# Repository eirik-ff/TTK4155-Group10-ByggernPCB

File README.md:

# TTK4155-Group10-ByggernPCB
The PCB files for the NTNU course Byggern (TTK4155 - Embedded and Industrial Computer Systems Design). 

# Schematic

# PCB Render

## Notes

USB module doesn't work.

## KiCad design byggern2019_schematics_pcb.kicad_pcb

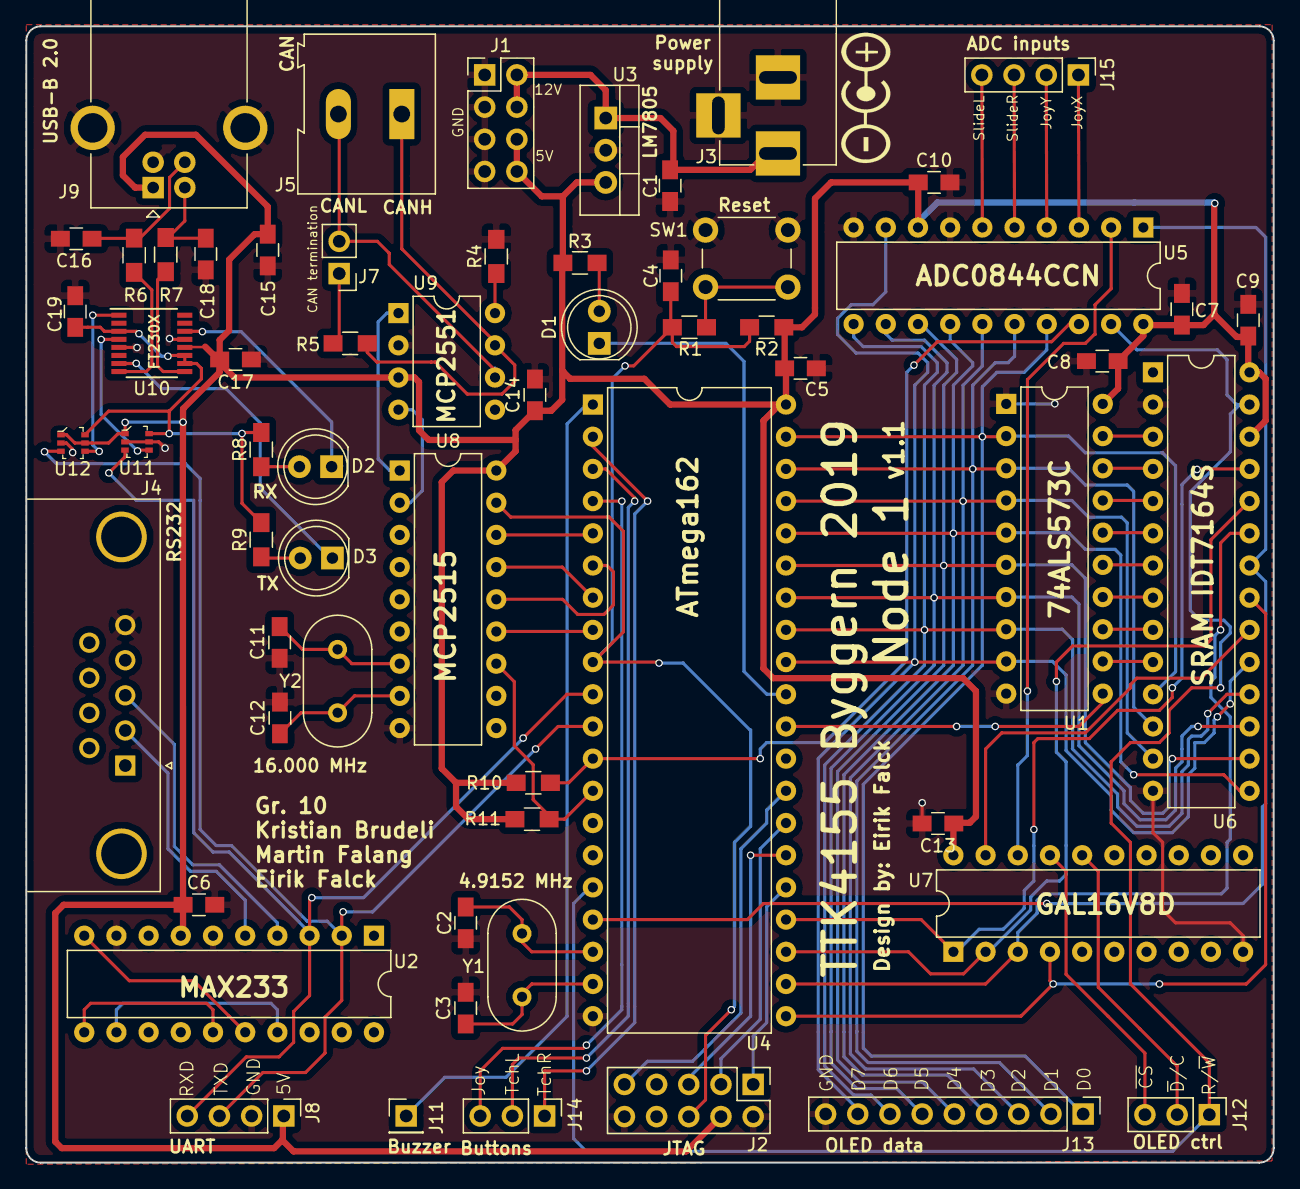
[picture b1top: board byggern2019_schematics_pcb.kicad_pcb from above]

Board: 2 copper layers, 98.4 x 89.7 mm, 61 parts (0 on the bottom side), 80 nets.

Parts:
C1, C4, C5, C6, C7, C8, C9, C10, C13, C14, C15, C19: 1u; C_0805_HandSoldering
C2, C3, C11, C12: 22p; C_0805_HandSoldering
C16, C18: 47p; C_0805_HandSoldering
C17: 10n; C_0805_HandSoldering
D1: Heartbeat; LED_D5.0mm
D2: ~RXLED; LED_D5.0mm
D3: ~TXLED; LED_D5.0mm
J1: Power; Pin_Header_Straight_2x04_Pitch2.54mm
J2: JTAG; Pin_Header_Straight_2x05_Pitch2.54mm
J3: Power supply; BARREL_JACK
J4: DB9_RS232_female; DSUB-9_Female_Horizontal_Pitch2.77x2.84mm_EdgePinOffset4.94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
J5: CAN; TerminalBlock_Altech_AK300-2_P5.00mm
J7: CAN terminate; Pin_Header_Straight_1x02_Pitch2.54mm
J8: UART; Pin_Header_Straight_1x04_Pitch2.54mm
J9: USB_B; USB_B_OST_USB-B1HSxx_Horizontal
J11: Buzzer; Pin_Header_Straight_1x01_Pitch2.54mm
J12: OLED Select; Pin_Header_Straight_1x03_Pitch2.54mm
J13: OLED data; Pin_Header_Straight_1x09_Pitch2.54mm
J14: Buttons; Pin_Header_Straight_1x03_Pitch2.54mm
J15: ADC inputs; Pin_Header_Straight_1x04_Pitch2.54mm
R1, R3, R8, R9: 330R; R_0805_HandSoldering
R2, R10, R11: 10k; R_0805_HandSoldering
R4: 22k; R_0805_HandSoldering
R5: 120R; R_0805_HandSoldering
R6, R7: 27R; R_0805_HandSoldering
SW1: Ext. reset; SW_PUSH_6mm
U1: SN74ALS573C; DIP-20_W7.62mm
U2: MAX233; DIP-20_W7.62mm
U3: LM7805_TO220; TO-220-3_Vertical
U4: ATMEGA162-16PU; DIP-40_W15.24mm
U5: ADC0844CCN; DIP-20_W7.62mm
U6: SRAM_IDT7164SL; DIP-28_W7.62mm
U7: GAL16V8D-15QP; DIP-20_W7.62mm
U8: MCP2515; DIP-18_W7.62mm
U9: MCP2551-I/P; DIP-8_W7.62mm
U10: FT230X; SSOP-16_3.9x4.9mm_Pitch0.635mm
U11, U12: 74LVC1T45; SOT-363
Y1: 4.9152 MHz; Resonator-2pin_w10.0mm_h5.0mm
Y2: 16.000 MHz; Resonator-2pin_w10.0mm_h5.0mm

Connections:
+3V3: C19.1, R8.2, R9.2, U10.3, U10.10, U10.11, U11.6, U12.6
+5V: C5.2, C6.1, C7.1, C8.1, C9.1, C10.1, C13.1, C14.1, C15.1, C17.1, J1.6, J1.8, J2.4, J8.1, J9.1, R2.1, R3.1, R10.2, R11.1, U1.20, U2.7, U3.3, U4.40, U5.8, U5.20, U6.26, U6.28, U7.20, U8.18, U9.3, U10.12, U11.1, U12.1, U12.5
+12V: C1.1, J1.2, J1.4, J3.1, U3.1
/A8: U4.21, U6.21, U7.4
/A9: U4.22, U6.23, U7.3
/A10: U4.23, U6.24, U7.2
/A11: U4.24, U6.25, U7.1
ADC_~CS: U5.2, U7.18
ADC_~INT: R10.1, U4.12, U5.18
Buzzer: J11.1, U4.1
CAN_~INT: R11.2, U4.13, U8.12
GND: C1.2, C2.2, C3.2, C4.2, C5.1, C6.2, C7.2, C8.2, C9.2, C10.2, C11.2, C12.2, C13.2, C14.2, C15.2, C16.2, C17.2, C18.2, C19.2, J1.1, J1.3, J1.5, J1.7, J2.2, J2.10, J3.2, J3.3, J4.5, J8.2, J9.4, J9.5, J13.9, R4.2, SW1.1, U1.1, U1.10, U2.6, U2.9, U3.2, U4.20, U5.7, U5.10, U6.2, U6.14, U7.10, U8.9, U9.2, U10.5, U10.13, U11.2, U11.5, U12.2
Heartbeat: D1.1, U4.31
JOY_BTN: J14.3, U4.4
JOY_X: J15.1, U5.3
JOY_Y: J15.2, U5.4
JTAG_RESET: C4.1, J2.6, R1.1, R2.2, U4.9, U8.17
JTAG_TCK: J2.1, U4.25
JTAG_TDI: J2.9, U4.28
JTAG_TDO: J2.3, U4.27
JTAG_TMS: J2.5, U4.26
unnamed: C2.1, U4.18, Y1.2
unnamed: C3.1, U4.19, Y1.1
unnamed: C11.1, U8.7, Y2.2
unnamed: C12.1, U8.8, Y2.1
unnamed: C16.1, J9.3, R6.2
unnamed: C18.1, J9.2, R7.2
unnamed: D1.2, R3.2
unnamed: D2.1, U10.14
unnamed: D2.2, R8.1
unnamed: D3.1, U10.7
unnamed: D3.2, R9.1
unnamed: J5.1, R5.1, U9.7
unnamed: J5.2, J7.2, U9.6
unnamed: J7.1, R5.2
unnamed: R1.2, SW1.2
unnamed: R4.1, U9.8
unnamed: R6.1, U10.8
unnamed: R7.1, U10.9
unnamed: U1.12, U6.10
unnamed: U1.13, U6.9
unnamed: U1.14, U6.8
unnamed: U1.15, U6.7
unnamed: U1.16, U6.6
unnamed: U1.17, U6.5
unnamed: U1.18, U6.4
unnamed: U1.19, U6.3
unnamed: U2.10, U2.16
unnamed: U2.11, U2.15
unnamed: U2.12, U2.17
RS232_RX: J4.3, U2.4
RS232_TX: J4.2, U2.5
RXCAN: U8.2, U9.4
SDB0: J13.1, U1.2, U4.39, U5.17, U6.11
SDB1: J13.2, U1.3, U4.38, U5.16, U6.12
SDB2: J13.3, U1.4, U4.37, U5.15, U6.13
SDB3: J13.4, U1.5, U4.36, U5.14, U6.15
SDB4: J13.5, U1.6, U4.35, U5.13, U6.16
SDB5: J13.6, U1.7, U4.34, U5.12, U6.17
SDB6: J13.7, U1.8, U4.33, U5.11, U6.18
SDB7: J13.8, U1.9, U4.32, U5.9, U6.19
SPI_MISO: U4.7, U8.15
SPI_MOSI: U4.6, U8.14
SPI_SCK: U4.8, U8.13
SPI_SS: U4.5, U8.16
SRAM_~CS: U6.20, U7.19
SliderL: J15.4, U5.6
SliderR: J15.3, U5.5
TXCAN: U8.1, U9.1
TouchBtnL: J14.2, U4.3
TouchBtnR: J14.1, U4.2
UART_RXD: J8.4, U2.3, U4.10, U11.3
UART_TXD: J8.3, U2.2, U4.11, U12.3
USB_UART_RXD: U10.4, U11.4
USB_UART_TXD: U10.1, U12.4
XMEM_ALE: U1.11, U4.30
XMEM_~RD: U4.17, U5.1, U6.22
XMEM_~WR: J12.1, U4.16, U5.19, U6.27
oled~CS: J12.3, U7.17
oled~D~/C: J12.2, U7.16

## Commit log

2019-12-06 Add all PCB files to repo
2019-12-06 Write readme
2019-12-06 Fix name typo
